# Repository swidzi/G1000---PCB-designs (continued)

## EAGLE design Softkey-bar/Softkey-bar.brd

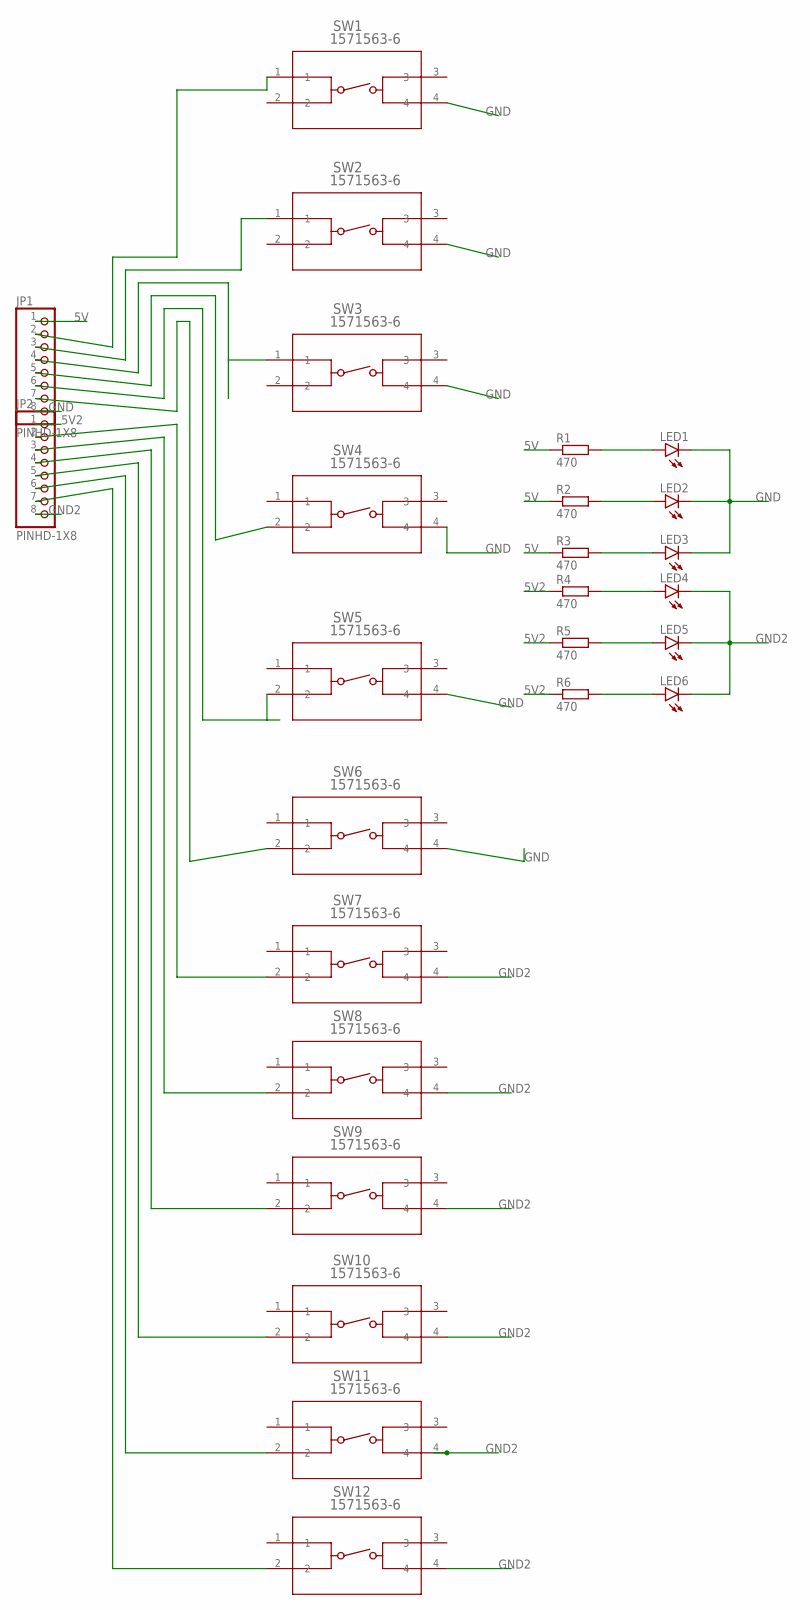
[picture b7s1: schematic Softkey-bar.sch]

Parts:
JP1, JP2: PINHD-1X8; 1X08
LED1, LED2, LED3, LED4, LED5, LED6: LEDCHIPLED_1206; CHIPLED_1206
R1, R2, R3, R4, R5, R6: 470; R0805
SW1, SW2, SW3, SW4, SW5, SW6, SW7, SW8, SW9, SW10, SW11, SW12: 1571563-6; SW4_1437565-E

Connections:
5V: JP1.1, R1.1, R2.1, R3.1
5V2: JP2.1, R4.1, R5.1, R6.1
GND: JP1.8, LED1.C, LED2.C, LED3.C, SW1.4, SW2.4, SW3.4, SW4.4, SW5.4, SW6.4
GND2: JP2.8, LED4.C, LED5.C, LED6.C, SW7.4, SW8.4, SW9.4, SW10.4, SW11.4, SW12.4
unnamed: JP1.2, SW1.1
unnamed: JP1.3, SW2.1
unnamed: JP1.4, SW3.1
unnamed: JP1.5, SW4.2
unnamed: JP1.6, SW5.2
unnamed: JP1.7, SW6.2
unnamed: LED1.A, R1.2
unnamed: LED2.A, R2.2
unnamed: LED3.A, R3.2
unnamed: LED4.A, R4.2
unnamed: LED5.A, R5.2
unnamed: LED6.A, R6.2
unnamed: JP2.2, SW7.2
unnamed: JP2.3, SW8.2
unnamed: JP2.4, SW9.2
unnamed: JP2.5, SW10.2
unnamed: JP2.6, SW11.2
unnamed: JP2.7, SW12.2

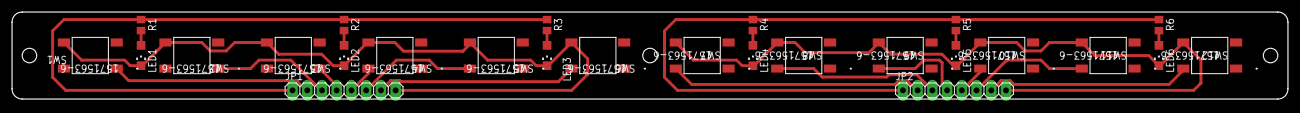
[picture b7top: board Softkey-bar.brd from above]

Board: 2 copper layers, 220.0 x 15.0 mm, 26 parts (0 on the bottom side), 22 nets.

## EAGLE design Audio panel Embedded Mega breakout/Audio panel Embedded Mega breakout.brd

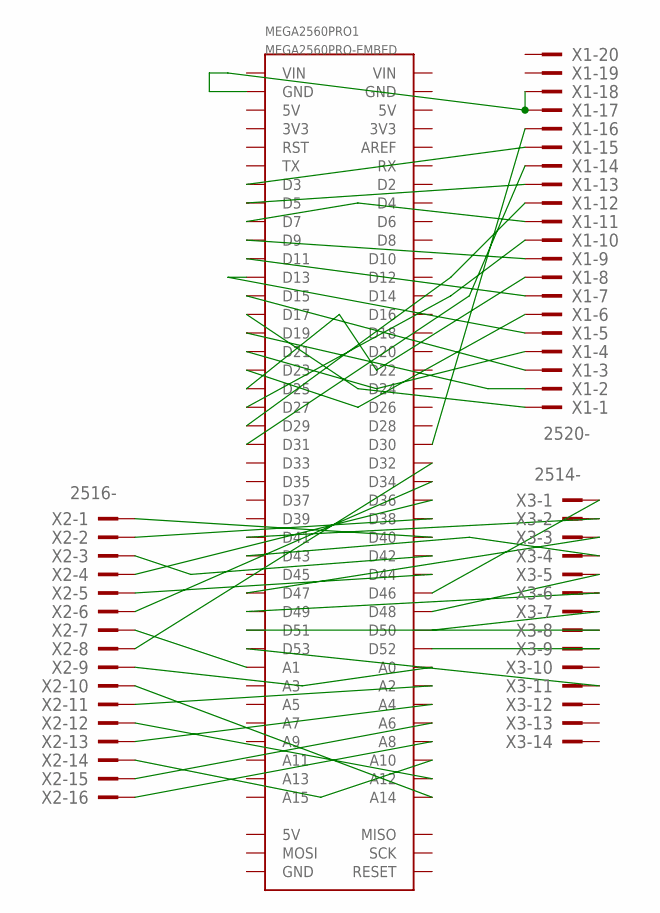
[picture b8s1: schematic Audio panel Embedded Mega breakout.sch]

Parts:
MEGA2560PRO1: MEGA2560PRO-EMBED
X1: 2520-; PAK100/2500-20
X2: 2516-; PAK100/2500-16
X3: 2514-; PAK100/2500-14

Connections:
unnamed: MEGA2560PRO1.D30, X1.16
unnamed: MEGA2560PRO1.GND@1 (GND), X1.17, X1.18
unnamed: MEGA2560PRO1.D31, X1.14
unnamed: MEGA2560PRO1.D29, X1.12
unnamed: MEGA2560PRO1.D27, X1.10
unnamed: MEGA2560PRO1.D25, X1.8
unnamed: MEGA2560PRO1.D23, X1.6
unnamed: MEGA2560PRO1.D21, X1.4
unnamed: MEGA2560PRO1.D7, X1.11
unnamed: MEGA2560PRO1.D19, X1.2
unnamed: MEGA2560PRO1.D17, X1.1
unnamed: MEGA2560PRO1.D15, X1.3
unnamed: MEGA2560PRO1.D13, X1.5
unnamed: MEGA2560PRO1.D11, X1.7
unnamed: MEGA2560PRO1.D9, X1.9
unnamed: MEGA2560PRO1.D5, X1.13
unnamed: MEGA2560PRO1.D3, X1.15
unnamed: MEGA2560PRO1.D38, X2.2
unnamed: MEGA2560PRO1.D53, X3.11
unnamed: MEGA2560PRO1.D52, X3.9
unnamed: MEGA2560PRO1.D50, X3.7
unnamed: MEGA2560PRO1.D48, X3.5
unnamed: MEGA2560PRO1.D47, X3.3
unnamed: MEGA2560PRO1.D46, X3.1
unnamed: MEGA2560PRO1.D51, X3.8
unnamed: MEGA2560PRO1.D49, X3.6
unnamed: MEGA2560PRO1.D43, X3.4
unnamed: MEGA2560PRO1.D41, X3.2
unnamed: MEGA2560PRO1.D36, X2.4
unnamed: MEGA2560PRO1.D34, X2.6
unnamed: MEGA2560PRO1.D32, X2.8
unnamed: MEGA2560PRO1.A14, X2.10
unnamed: MEGA2560PRO1.A12, X2.12
unnamed: MEGA2560PRO1.A10, X2.14
unnamed: MEGA2560PRO1.A8, X2.16
unnamed: MEGA2560PRO1.A6, X2.15
unnamed: MEGA2560PRO1.A4, X2.13
unnamed: MEGA2560PRO1.A2, X2.11
unnamed: MEGA2560PRO1.A0, X2.9
unnamed: MEGA2560PRO1.A1, X2.7
unnamed: MEGA2560PRO1.D40, X2.1
unnamed: MEGA2560PRO1.D42, X2.3
unnamed: MEGA2560PRO1.D44, X2.5

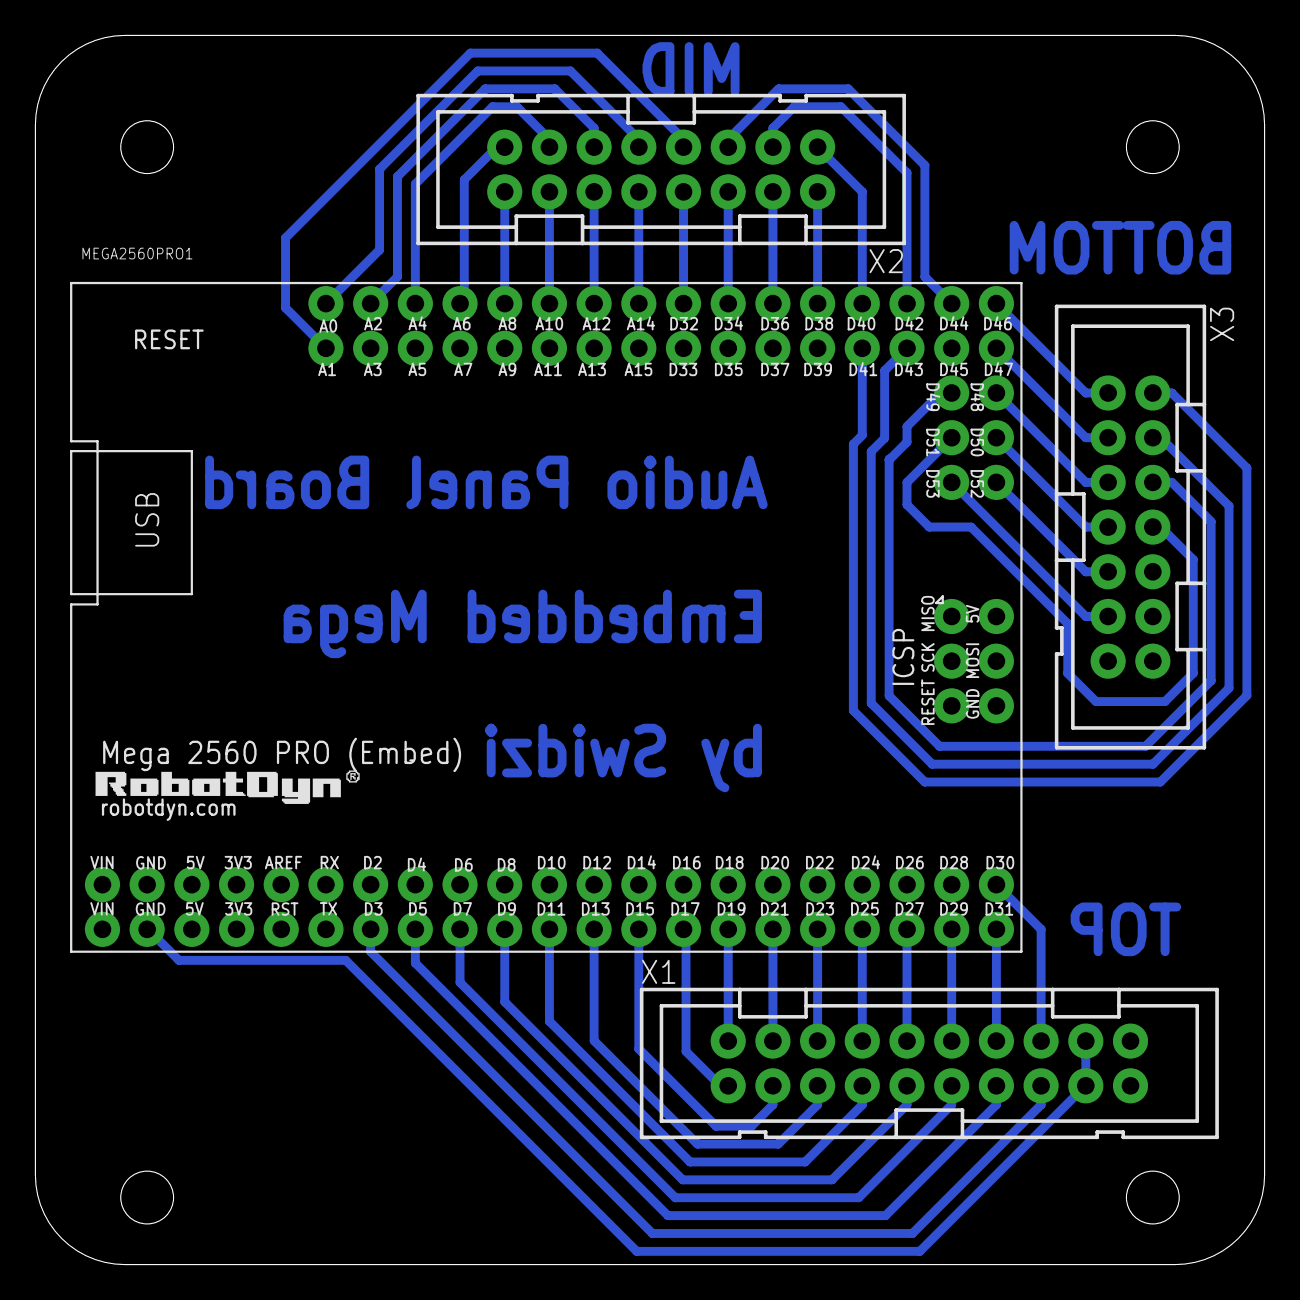
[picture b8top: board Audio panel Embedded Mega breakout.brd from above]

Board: 2 copper layers, 69.8 x 69.8 mm, 4 parts (0 on the bottom side), 43 nets.

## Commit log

2021-01-18 Initial release.
2021-01-18 Create LICENSE
2021-01-18 Changed drill size to 2.05mm, moved drills in AP board
2021-01-18 no message
2021-01-18 Added G1000 connection chart.png
2021-01-18 Small correction to epf
2021-01-18 Added Audio Board G1000.png
2021-01-18 General clean-up
2021-01-19 Renamed panel to fit 12.1 inch panel
2021-01-30 New Audio Panel
